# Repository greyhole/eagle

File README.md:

eagle
=====

eagle project directory

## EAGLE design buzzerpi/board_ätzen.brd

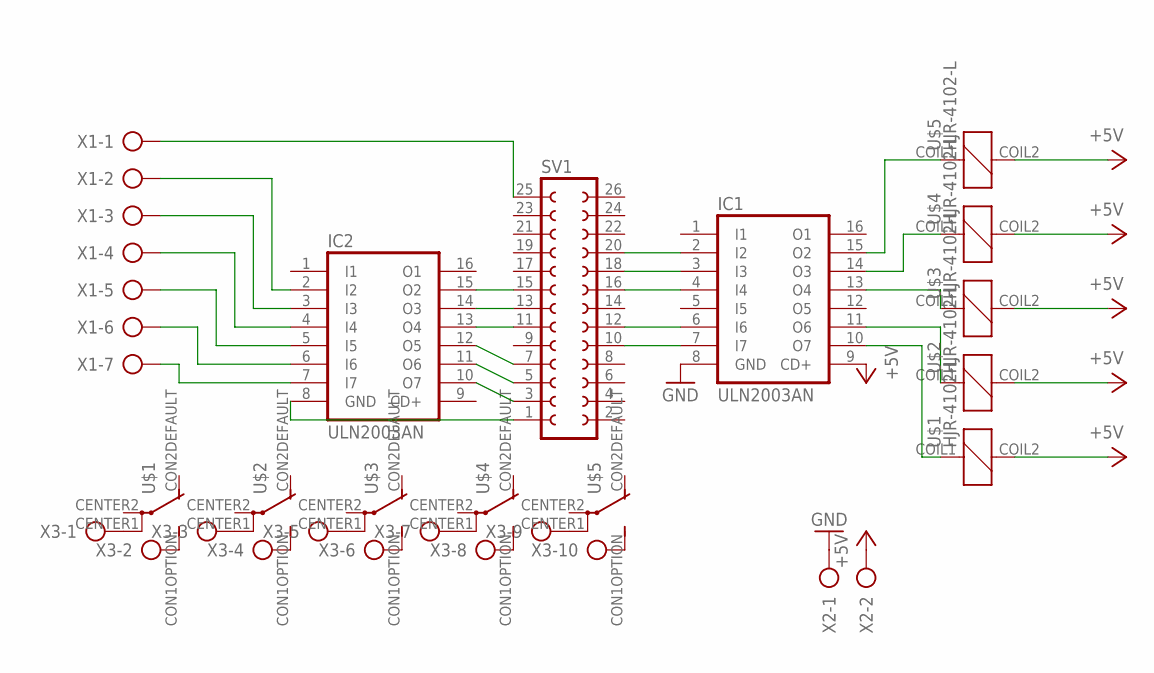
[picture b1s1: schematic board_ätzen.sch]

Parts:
IC1, IC2: ULN2003AN; DIL16
SV1: FE13-2
U$1, U$2, U$3, U$4, U$5: HJR-4102-L; HJR4102
X1: AK500/7
X2: AK500/2
X3: AK500/10

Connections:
+5V: IC1.9 (CD+), U$1.COIL2 (2), U$2.COIL2 (2), U$3.COIL2 (2), U$4.COIL2 (2), U$5.COIL2 (2), X2.2
GND: IC1.8 (GND), X2.1
unnamed: IC2.8 (GND), SV1.1
unnamed: IC2.10 (O7), SV1.3
unnamed: IC2.11 (O6), SV1.5
unnamed: IC2.12 (O5), SV1.7
unnamed: IC2.13 (O4), SV1.11
unnamed: IC2.14 (O3), SV1.13
unnamed: IC2.15 (O2), SV1.15
unnamed: SV1.25, X1.1
unnamed: IC2.2 (I2), X1.2
unnamed: IC2.3 (I3), X1.3
unnamed: IC2.4 (I4), X1.4
unnamed: IC2.5 (I5), X1.5
unnamed: IC2.6 (I6), X1.6
unnamed: IC2.7 (I7), X1.7
unnamed: IC1.7 (I7), SV1.10
unnamed: IC1.6 (I6), SV1.12
unnamed: IC1.2 (I2), SV1.20
unnamed: IC1.4 (I4), SV1.16
unnamed: IC1.15 (O2), U$5.COIL1 (1)
unnamed: IC1.14 (O3), U$4.COIL1 (1)
unnamed: IC1.13 (O4), U$3.COIL1 (1)
unnamed: U$4.CENTER1, X3.7
unnamed: U$3.CON1OPTION (S), X3.6
unnamed: IC1.11 (O6), U$2.COIL1 (1)
unnamed: U$5.CENTER1, X3.9
unnamed: U$4.CON1OPTION (S), X3.8
unnamed: U$3.CENTER1, X3.5
unnamed: U$2.CON1OPTION (S), X3.4
unnamed: IC1.3 (I3), SV1.18
unnamed: IC1.10 (O7), U$1.COIL1 (1)
unnamed: U$2.CENTER1, X3.3
unnamed: U$1.CON1OPTION (S), X3.2
unnamed: U$1.CENTER1, X3.1
unnamed: U$5.CON1OPTION (S), X3.10

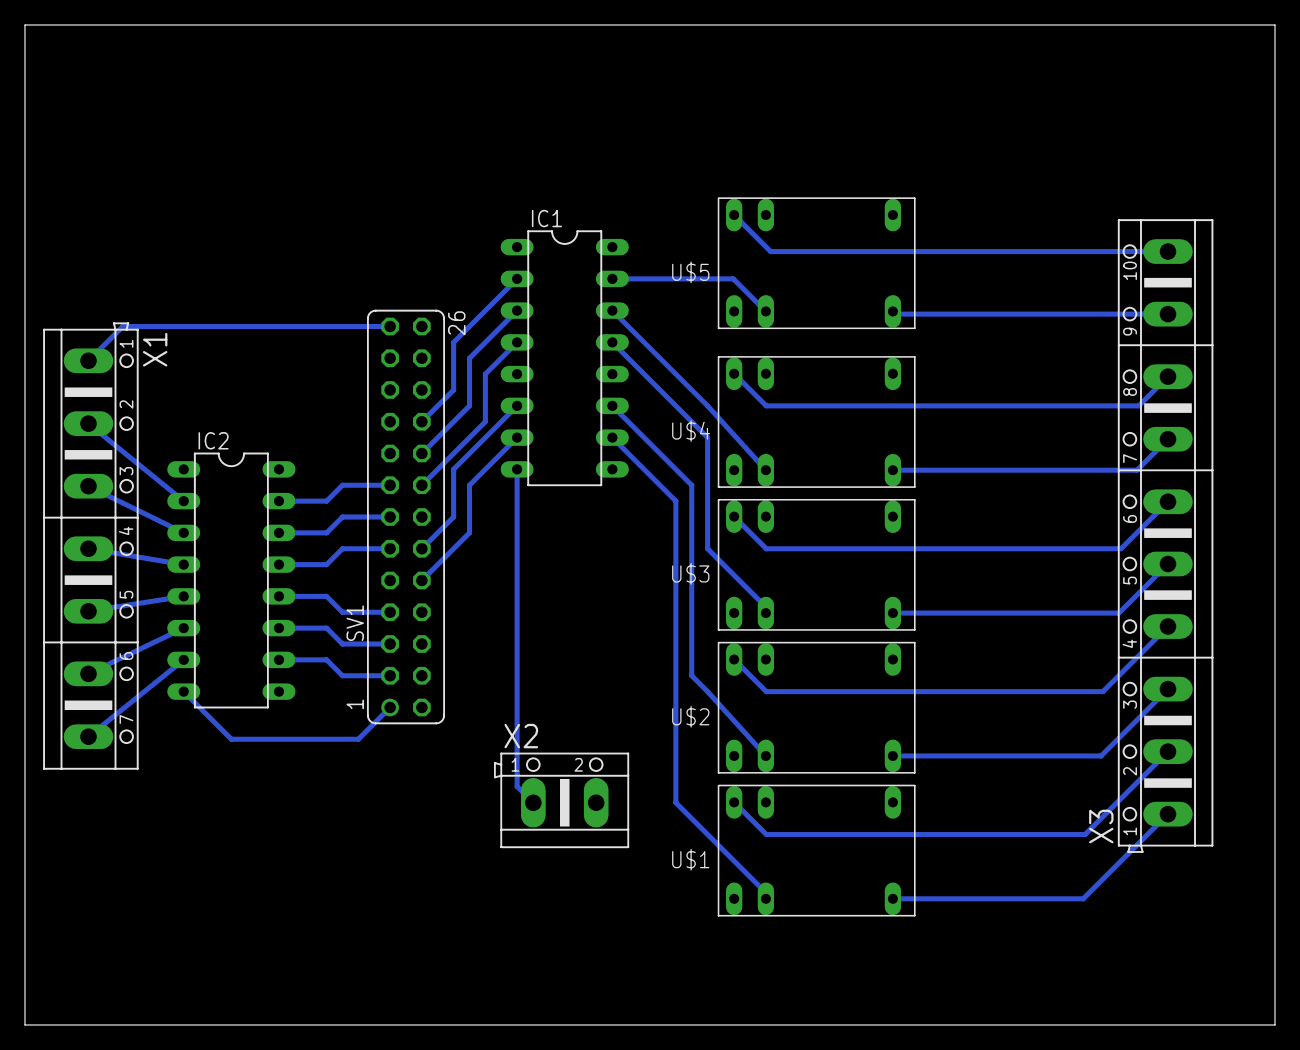
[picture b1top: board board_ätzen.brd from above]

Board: 2 copper layers, 100.0 x 80.0 mm, 11 parts (0 on the bottom side), 36 nets.

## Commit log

2014-04-08 buzzerpilayou
2014-04-08 layout geändert
2014-04-09 ätzboard hinzugefügt
2014-04-09 geändert
